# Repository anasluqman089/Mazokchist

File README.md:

# Mazokchist

*Hello Everyone!*

What is Mazokchist you might ask? it is a small environmental monitor built around the Seeed XIAO ESP32-C6, a e-ink diplay and a BME680

The sensor measures temperature, humidity, pressure and gas quality and sends
the readings over I2C to the XIAO, which displays them on a 2.9"
e-Paper screen.

Why the name is Mazokchist? It is just a msde up name no need to know the meaning.

## How it works

- **BME680** — reads temperature, humidity, pressure and gas quality then 
  sends that data to the XIAO over I2C.
- **XIAO ESP32-C6** — reads the sensor using I2C and drives the display using SPI.
- **Waveshare 2.9" e-Paper** — shows the latest readings. The screen refreshes
  once a minute.

## Bill of Materials

| Qty | Component                                    | Category    | Price (USD) | Buy Link                                                                                              | Notes                                                             |
| --: | -------------------------------------------- | ----------- | ----------: | ----------------------------------------------------------------------------------------------------- | ----------------------------------------------------------------- |
|   1 | Seeed XIAO ESP32-C6                          | Electronics |       $5.20 | [Seeed Studio](https://www.seeedstudio.com/Seeed-Studio-XIAO-ESP32C6-p-5884.html)                     | MCU |
|   1 | BME680 Breakout Module                       | Electronics |      $13.99 | [Amazon](https://www.amazon.com/HiLetgo-Temperature-Precision-Environmental-Monitoring/dp/B0CDWXZNY7) | Enviromental Sensor |
|   1 | Waveshare 2.9 inch E-Paper Module V2 SSD1680 | Electronics |      $21.99 | [Waveshare](https://www.waveshare.com/product/displays/e-paper/2.9inch-e-paper-module.htm)            | 296×128 monochrome e-paper display |
|   1 | JST PH 2.0mm 8-Pin SMT Header                | Electronics |      ~$1.00 | —                                                                                                     | For the PCB                                                       |
|   1 | JST PH 2.0mm 8-Pin Cable                     | Electronics |      ~$2.00 | —                                                                                                     | Connecting the PCB to the display                                 |
|   4 | M3 × 20mm Screw                              | Hardware    |      ~$2.00 | —                                                                                                     | Securing the PCB                                                  |
|   4 | M3 × 6mm Screw                               | Hardware    |      ~$2.00 | —                                                                                                     | Securing the case                                                 |
|   4 | M3 Standoff                                  | Hardware    |      ~$1.00 | —                                                                                                     | PCB/display spacers                                               |
|   1 | 3D Printed Enclosure                         | Mechanical  |      ~$5.00 | —                                                                                                     | PLA or PETG enclosure                                             |

## Estimated Total

**≈ $56.18 USD** (Not including shipping)

## Wiring

| BME680 | XIAO pin |
|---|---|
| VCC | 3V3 |
| GND | GND |
| SDA | D4 |
| SCL | D5 |
| SDO | GND |
| CS | 3V3 |

| e-Paper (J1) | XIAO pin |
|---|---|
| VCC | 3V3 |
| GND | GND |
| DIN | D10 |
| CLK | D8 |
| CS | D3 |
| DC | D2 |
| RST | D1 |
| BUSY | D0 |

**Notice** : BME680 SDO is conected to GND which sets its I2C address to 0x76. BME680 CS is connected to 3V3
which forces the module into I2C mode.

## Assemble the hardware and firmware
1. Fabricate the PCB from the KiCad project (or wire the parts manually on protoboard using the wiring table above).
2. Solder the XIAO ESP32-C6, the BME680 module (directly onto its PCB pads), and the JST PH 2.0mm 8-pin SMT header onto the board.
3. Connect the Waveshare 2.9" e-Paper display to the JST PH header using the JST PH 2.0mm cable.
4. Mount the board using the 4 mounting holes, M3 screws, standoffs and nuts.
5. Use Arduino IDE and download all the libraries
6. Upload the code
7. *Power it on!*

## Images

### Schematic

### PCB

### CAD

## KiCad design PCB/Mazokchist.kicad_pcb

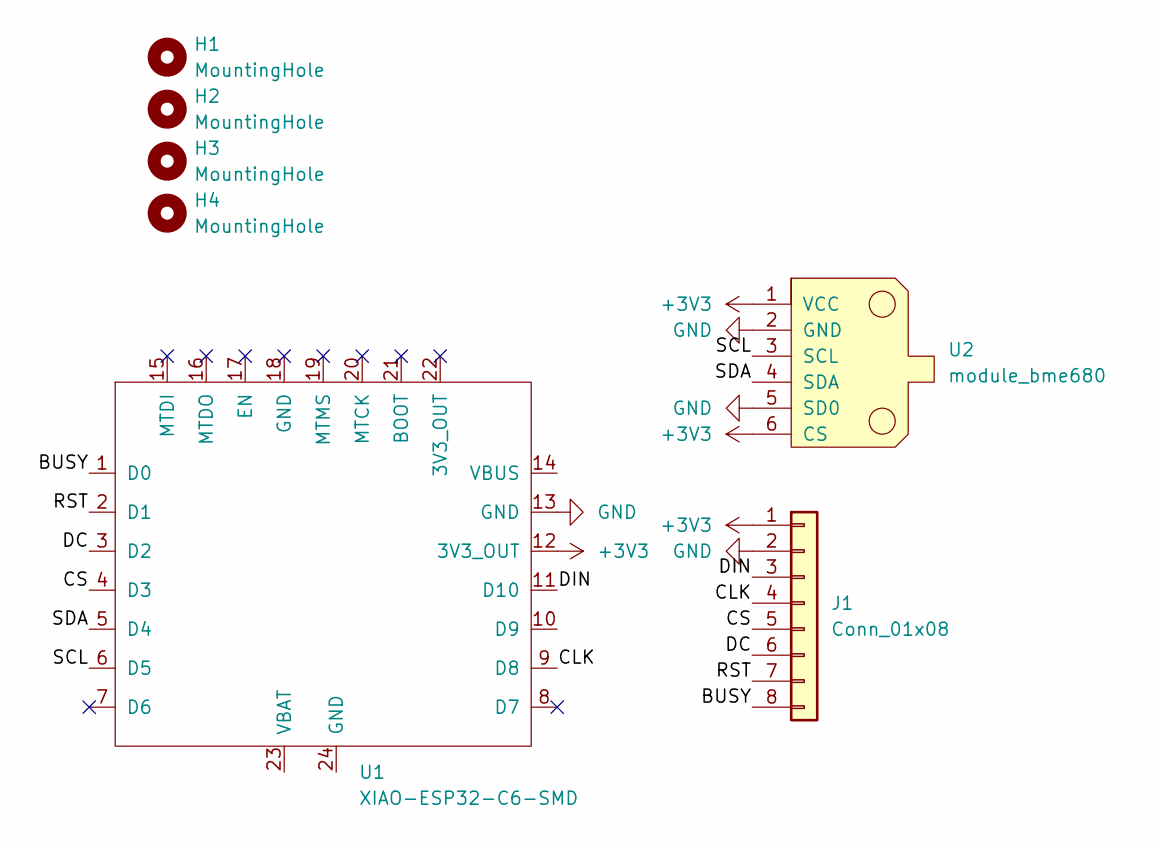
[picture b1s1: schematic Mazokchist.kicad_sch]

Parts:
H1, H2, H3, H4: MountingHole; MountingHole_2.7mm_M2.5
J1: Conn_01x08; JST_PH_B8B-PH-K_1x08_P2.00mm_Vertical
U1: XIAO-ESP32-C6-SMD; XIAO-ESP32-C6-DIP
U2: module_bme680

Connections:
+3V3: J1.1, U1.12 (3V3_OUT), U2.1 (VCC), U2.6 (CS)
/BUSY: J1.8, U1.1 (D0)
/CLK: J1.4, U1.9 (D8)
/CS: J1.5, U1.4 (D3)
/DC: J1.6, U1.3 (D2)
/DIN: J1.3, U1.11 (D10)
/RST: J1.7, U1.2 (D1)
/SCL: U1.6 (D5), U2.3 (SCL)
/SDA: U1.5 (D4), U2.4 (SDA)
GND: J1.2, U1.13 (GND), U2.2 (GND), U2.5 (SD0)

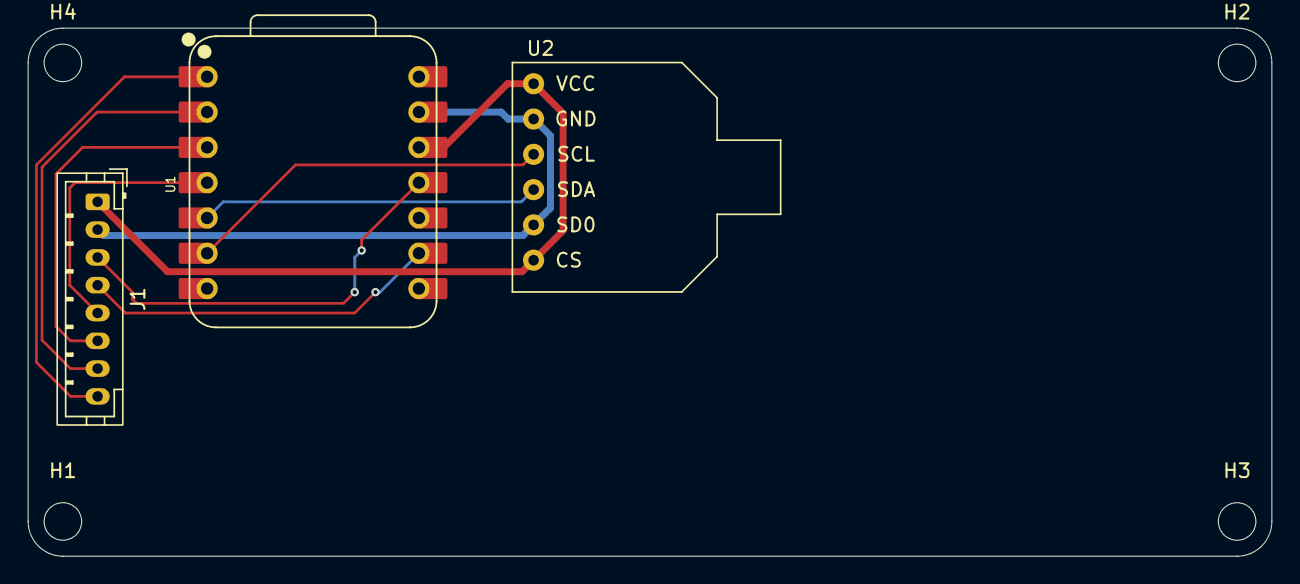
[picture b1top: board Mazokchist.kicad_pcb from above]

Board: 2 copper layers, 89.5 x 38.0 mm, 7 parts (0 on the bottom side), 10 nets.
